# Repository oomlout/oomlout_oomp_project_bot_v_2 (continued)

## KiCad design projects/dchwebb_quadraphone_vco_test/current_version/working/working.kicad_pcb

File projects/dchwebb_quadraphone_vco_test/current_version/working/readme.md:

# quadraphone
 
## summary 
* id: dchwebb_quadraphone_vco_test
* user: dchwebb
* name: quadraphone
* board: vco_test
* repo: https://github.com/dchwebb/Quadraphone
* src_file_repo_kicad_pcb: bu/Test_Board_Final/VCO_Test.kicad_pcb
* src_file_repo_kicad_pcb_link: https://github.com/dchwebb/Quadraphone/tree/main/bu/Test_Board_Final/VCO_Test.kicad_pcb
* src_file_repo_kicad_sch: bu/Test_Board_Final/VCO_Test.kicad_sch
* src_file_repo_kicad_sch_link: https://github.com/dchwebb/Quadraphone/tree/main/bu/Test_Board_Final/VCO_Test.kicad_sch

* src_file_repo_sch: 
* src_file_repo_sch_link: https://github.com/dchwebb/Quadraphone/tree/main/
* full details link: https://github.com/oomlout/oomlout_oomp_project_bot_v_2/tree/main/projects/dchwebb_quadraphone_vco_test/current_version/working

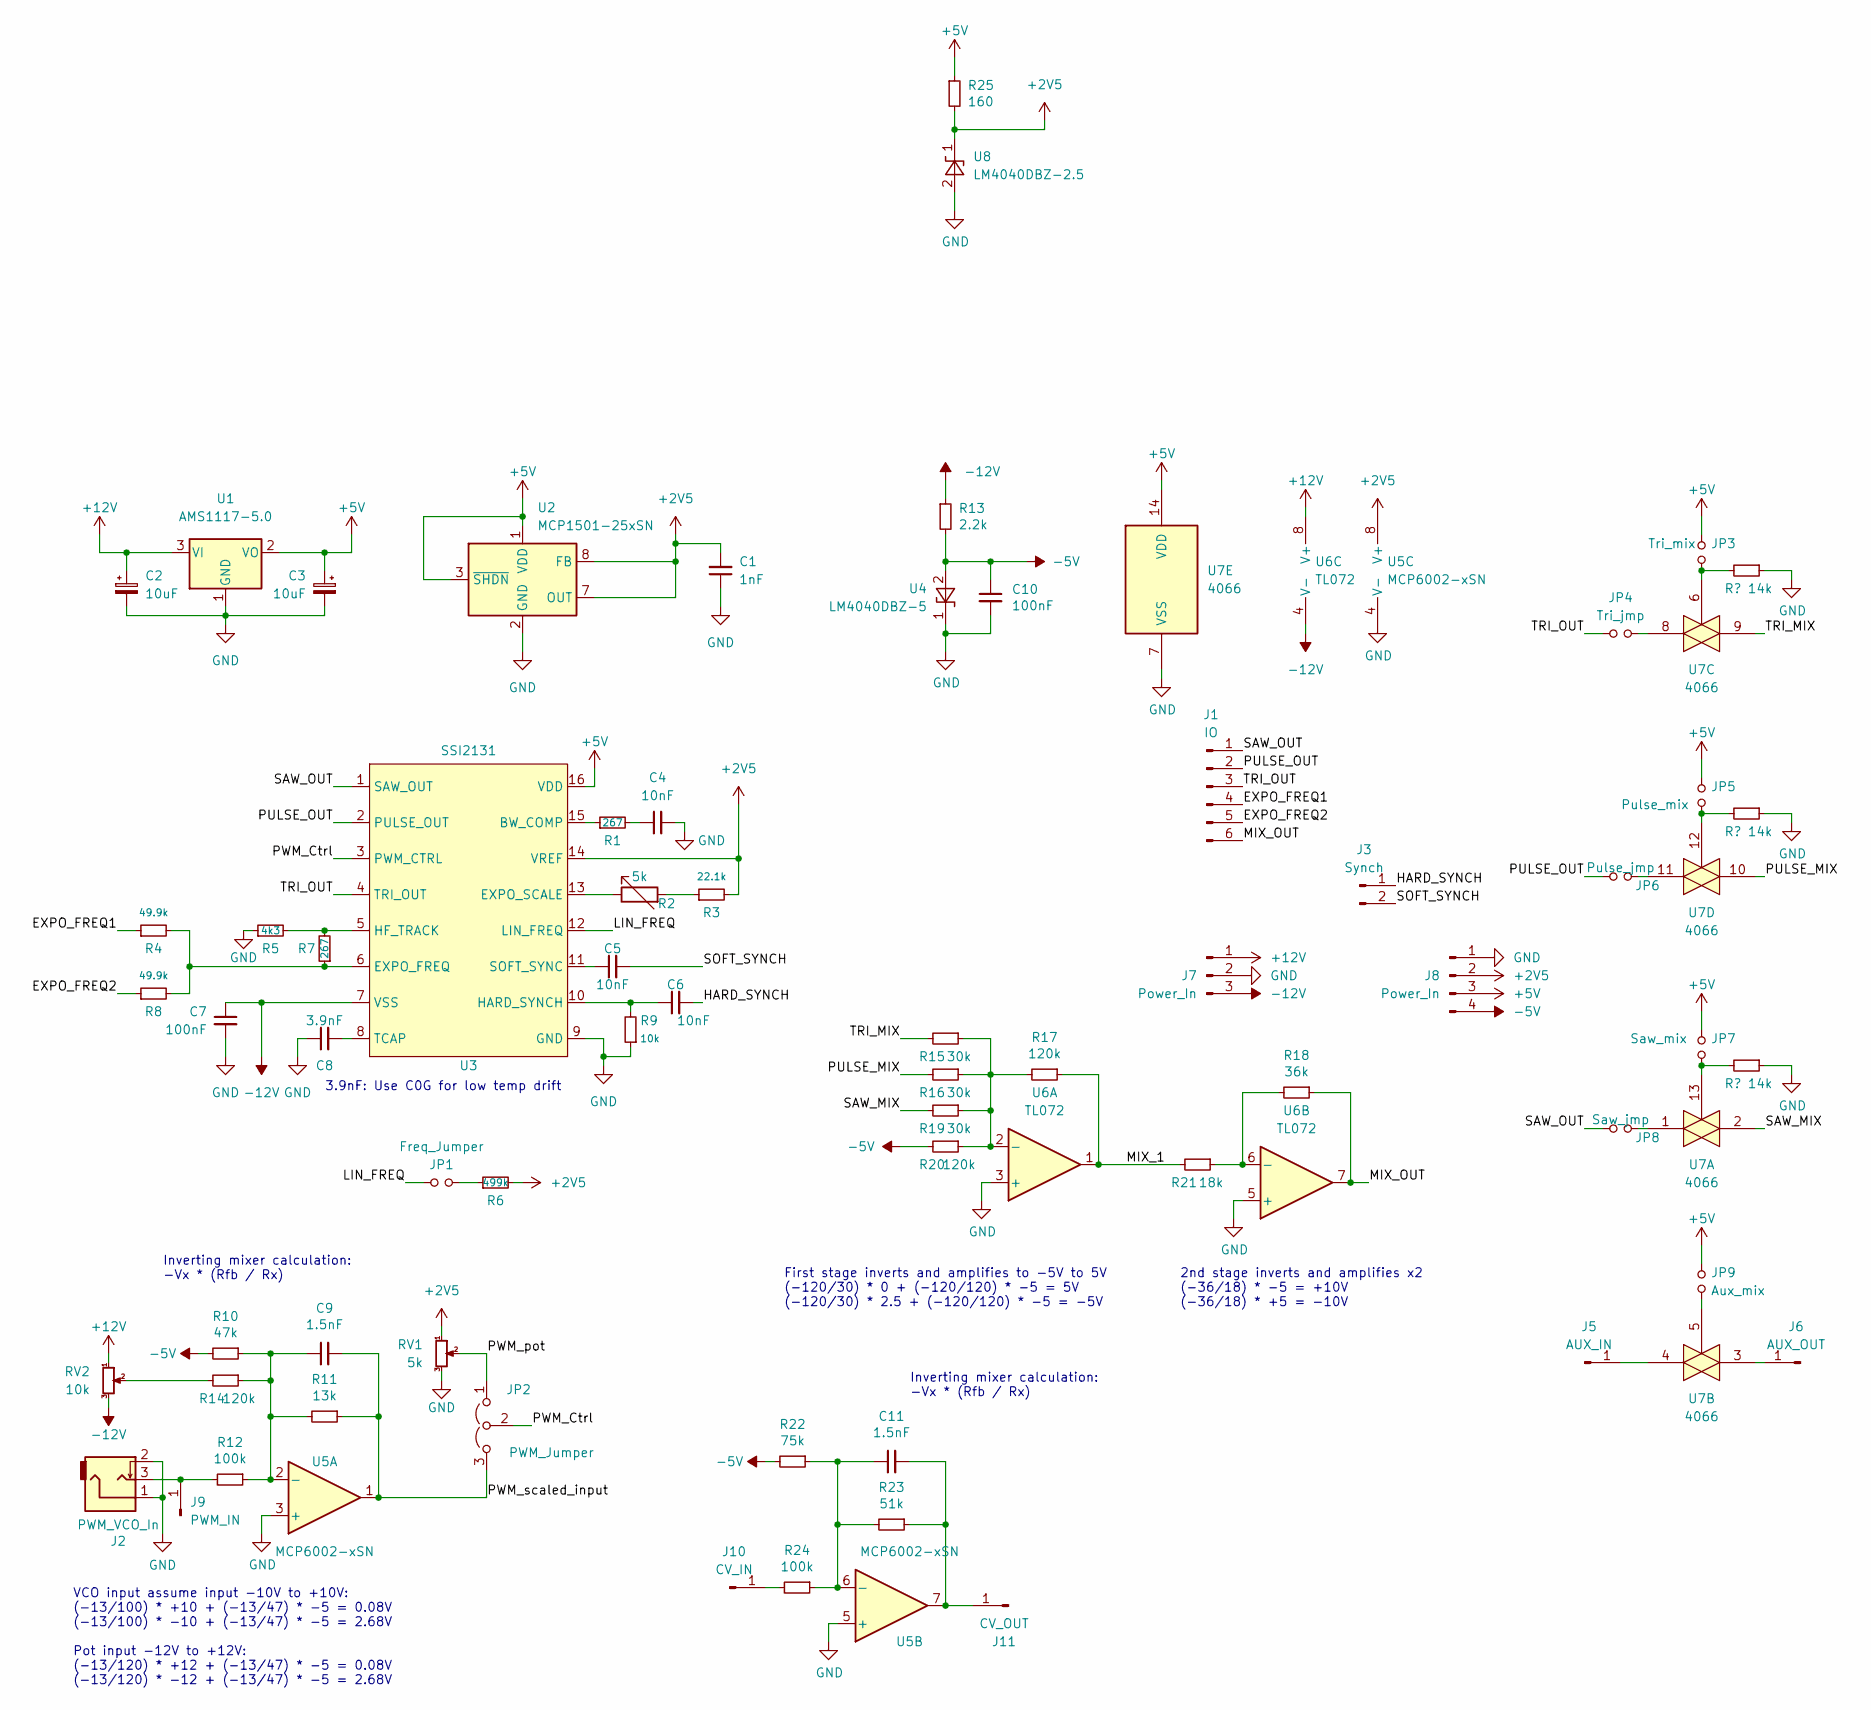
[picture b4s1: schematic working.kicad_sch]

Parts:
C1: 1nF; C_0805_2012Metric
C2, C3: 10uF; CP_Elec_5x5.7
C4, C5, C6: 10nF; C_0805_2012Metric
C7, C10: 100nF; C_0805_2012Metric
C8: 3.9nF; C_0805_2012Metric
C9, C11: 1.5nF; C_0805_2012Metric
J1: IO; PinHeader_1x06_P2.54mm_Vertical
J2: PWM_VCO_In; THONKICONN_hole
J3: Synch; PinHeader_1x02_P2.54mm_Vertical
J5: AUX_IN; PinHeader_1x01_P2.54mm_Vertical
J6: AUX_OUT; PinHeader_1x01_P2.54mm_Vertical
J7: Power_In; PinHeader_1x03_P2.54mm_Vertical
J8: Power_In; PinHeader_1x04_P2.54mm_Vertical
J9: PWM_IN; PinHeader_1x01_P2.54mm_Vertical
J10: CV_IN; PinHeader_1x01_P2.54mm_Vertical
J11: CV_OUT; PinHeader_1x01_P2.54mm_Vertical
JP1: Freq_Jumper; PinHeader_1x02_P2.54mm_Vertical
JP2: PWM_Jumper; PinHeader_1x03_P2.54mm_Vertical
JP3: Tri_mix; PinHeader_1x02_P2.54mm_Vertical
JP4: Tri_jmp; PinHeader_1x02_P2.54mm_Vertical
JP5: Pulse_mix; PinHeader_1x02_P2.54mm_Vertical
JP6: Pulse_jmp; PinHeader_1x02_P2.54mm_Vertical
JP7: Saw_mix; PinHeader_1x02_P2.54mm_Vertical
JP8: Saw_jmp; PinHeader_1x02_P2.54mm_Vertical
JP9: Aux_mix; PinHeader_1x02_P2.54mm_Vertical
R1, R7: 267; R_0805_2012Metric
R2: 5k; Potentiometer_Piher_PT-6-V_Vertical
R3: 22.1k; R_0805_2012Metric
R4, R8: 49.9k; R_0805_2012Metric
R5: 4k3; R_0805_2012Metric
R6: 499k; R_0805_2012Metric
R9: 10k; R_0805_2012Metric
R10: 47k; R_0805_2012Metric
R11: 13k; R_0805_2012Metric
R12, R24: 100k; R_0805_2012Metric
R13: 2.2k; R_0805_2012Metric
R14, R17, R20: 120k; R_0805_2012Metric
R15, R16, R19: 30k; R_0805_2012Metric
R18: 36k; R_0805_2012Metric
R21: 18k; R_0805_2012Metric
R22: 75k; R_0805_2012Metric
R23: 51k; R_0805_2012Metric
R25: 160; R_0805_2012Metric
RV1: 5k; Alpha_9mm_Potentiometer_Aligned
RV2: 10k; Alpha_9mm_Potentiometer_Aligned
U1: AMS1117-5.0; SOT-223-3_TabPin2
U2: MCP1501-25xSN; SOIC-8_3.9x4.9mm_P1.27mm
U3: SSI2131; SOIC-16_3.9x9.9mm_P1.27mm
U4: LM4040DBZ-5; SOT-23
U5: MCP6002-xSN; MSOP-8_3x3mm_P0.65mm
U6: TL072; SO-8_3.9x4.9mm_P1.27mm
U7: 4066; TSSOP-14_4.4x5mm_P0.65mm
U8: LM4040DBZ-2.5; SOT-23

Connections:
+2V5: C1.2, J8.2, R3.2, R6.2, R25.2, RV1.1, U2.7 (OUT), U2.8 (FB), U3.14 (VREF), U5.8 (V+), U8.1 (K)
+5V: C3.1, J8.3, JP3.2, JP5.2, JP7.2, JP9.2, R25.1, U1.2 (VO), U2.1 (VDD), U2.3 (~SHDN), U3.16 (VDD), U7.14 (VDD)
+12V: C2.1, J7.1, RV2.1, U1.3 (VI), U6.8 (V+)
-5V: C10.1, J8.4, R10.2, R13.2, R20.2, R22.2, U4.2 (A)
-12V: C7.1, J7.3, R13.1, RV2.3, U3.7 (VSS), U6.4 (V-)
/EXPO_FREQ1: J1.4, R4.1
/EXPO_FREQ2: J1.5, R8.1
/HARD_SYNCH: C6.2, J3.1
/LIN_FREQ: JP1.1, U3.12 (LIN_FREQ)
/MIX_1: R17.1, R21.2, U6.1
/MIX_OUT: J1.6, R18.1, U6.7
/PULSE_MIX: R16.2, U7.10
/PULSE_OUT: J1.2, JP6.1, U3.2 (PULSE_OUT)
/PWM_Ctrl: JP2.2 (C), U3.3 (PWM_CTRL)
/PWM_pot: JP2.1 (A), RV1.2
/PWM_scaled_input: C9.2, JP2.3 (B), R11.1, U5.1
/SAW_MIX: R19.2, U7.2
/SAW_OUT: J1.1, JP8.1, U3.1 (SAW_OUT)
/SOFT_SYNCH: C5.2, J3.2
/TRI_MIX: R15.2, U7.9
/TRI_OUT: J1.3, JP4.1, U3.4 (TRI_OUT)
GND: C1.1, C2.2, C3.2, C4.2, C7.2, C8.1, C10.2, J2.1, J2.2, J7.2, J8.1, R5.1, R9.1, RV1.3, U1.1 (GND), U2.2 (GND), U2.4 (GND), U2.5 (GND), U2.6 (GND), U3.9 (GND), U4.1 (K), U5.3 (+), U5.4 (V-), U5.5 (+), U6.3 (+), U6.5 (+), U7.7 (VSS), U8.2 (A)
unnamed: C4.1, R1.2
unnamed: C5.1, U3.11 (SOFT_SYNC)
unnamed: C6.1, R9.2, U3.10 (HARD_SYNCH)
unnamed: C8.2, U3.8 (TCAP)
unnamed: C9.1, R10.1, R11.2, R12.1, R14.1, U5.2 (-)
unnamed: C11.1, R22.1, R23.2, R24.1, U5.6 (-)
unnamed: C11.2, J11.1, R23.1, U5.7
unnamed: J2.3, J9.1, R12.2
unnamed: J5.1, U7.4
unnamed: J6.1, U7.3
unnamed: J10.1, R24.2
unnamed: JP1.2, R6.1
unnamed: JP3.1, U7.6
unnamed: JP4.2, U7.8
unnamed: JP5.1, U7.12
unnamed: JP6.2, U7.11
unnamed: JP7.1, U7.13
unnamed: JP8.2, U7.1
unnamed: JP9.1, U7.5
unnamed: R1.1, U3.15 (BW_COMP)
unnamed: R2.1, U3.13 (EXPO_SCALE)
unnamed: R2.2, R3.1
unnamed: R4.2, R7.1, R8.2, U3.6 (EXPO_FREQ)
unnamed: R5.2, R7.2, U3.5 (HF_TRACK)
unnamed: R14.2, RV2.2
unnamed: R15.1, R16.1, R17.2, R19.1, R20.1, U6.2 (-)
unnamed: R18.2, R21.1, U6.6 (-)

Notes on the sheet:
VCO input assume input -10V to +10V: (-13/100) * +10 + (-13/47) * -5 = 0.08V (-13/100) * -10 + (-13/47) * -5 = 2.68V Pot input -12V to +12V: (-13/120) * +12 + (-13/47) * -5 = 0.08V (-13/120) * -12 + (-13/47) * -5 = 2.68V
First stage inverts and amplifies to -5V to 5V (-120/30) * 0 + (-120/120) * -5 = 5V (-120/30) * 2.5 + (-120/120) * -5 = -5V
3.9nF: Use C0G for low temp drift
2nd stage inverts and amplifies x2 (-36/18) * -5 = +10V (-36/18) * +5 = -10V
Inverting mixer calculation: -Vx * (Rfb / Rx)

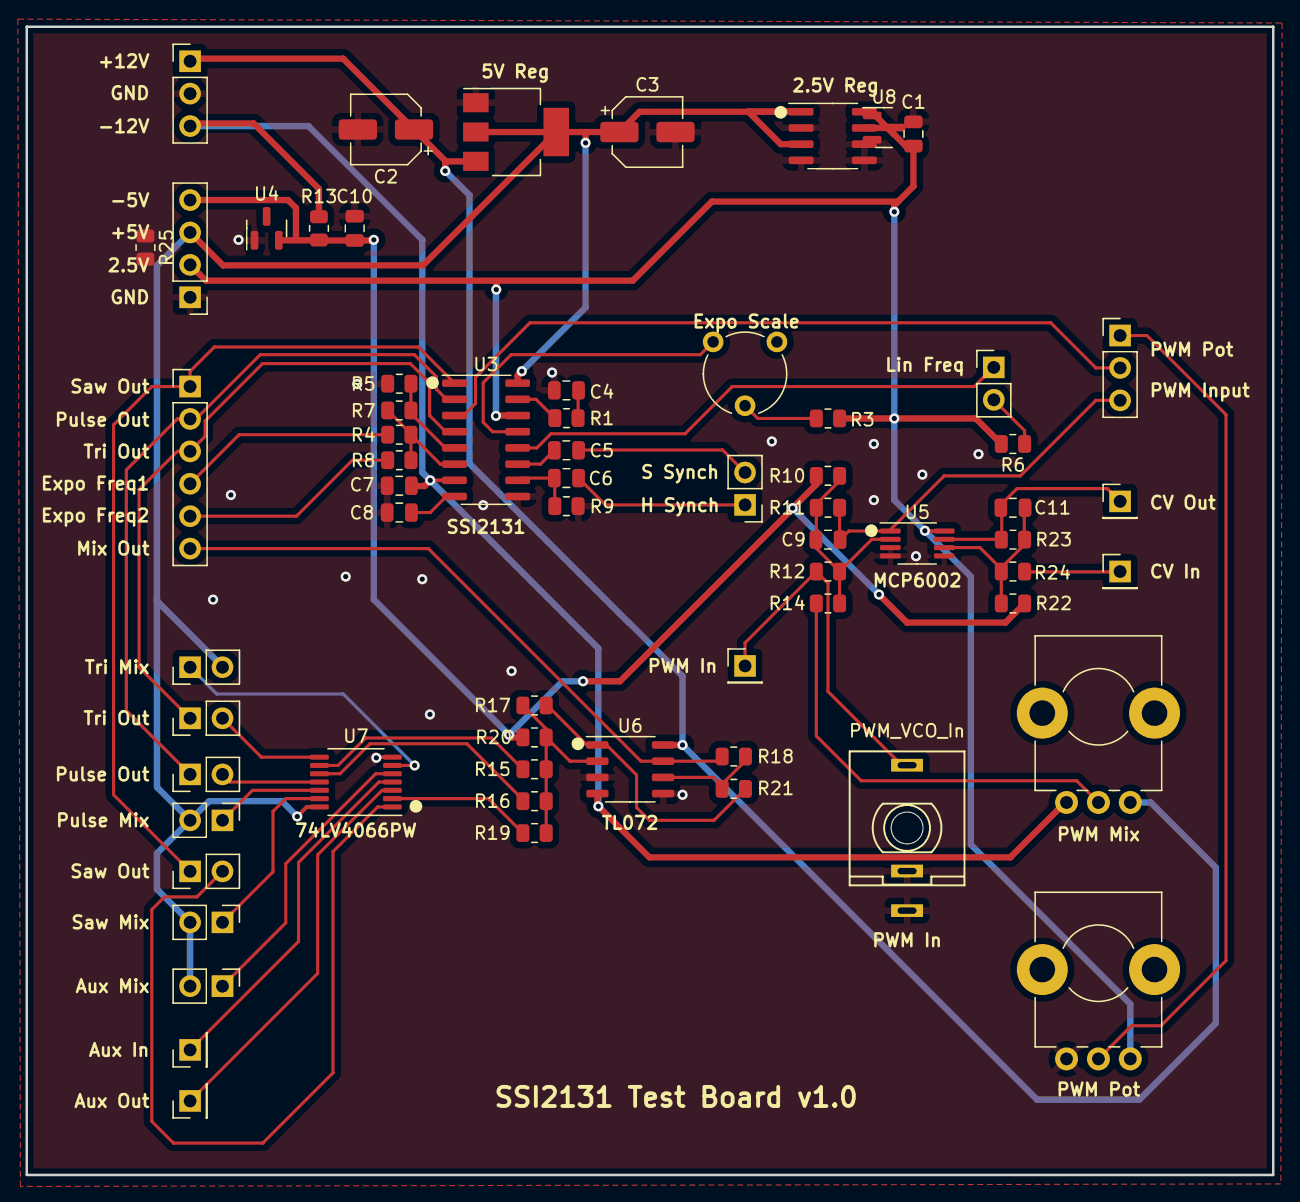
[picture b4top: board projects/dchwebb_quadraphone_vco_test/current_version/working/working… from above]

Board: 2 copper layers, 97.7 x 90.0 mm, 65 parts (0 on the bottom side), 49 nets.

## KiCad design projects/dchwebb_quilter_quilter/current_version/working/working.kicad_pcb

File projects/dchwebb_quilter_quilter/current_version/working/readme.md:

# quilter
 
## summary 
* id: dchwebb_quilter_quilter
* user: dchwebb
* name: quilter
* board: quilter
* repo: https://github.com/dchwebb/Quilter
* src_file_repo_kicad_pcb: Test_Board/Quilter.kicad_pcb
* src_file_repo_kicad_pcb_link: https://github.com/dchwebb/Quilter/tree/main/Test_Board/Quilter.kicad_pcb
* src_file_repo_kicad_sch: Test_Board/Quilter.kicad_sch
* src_file_repo_kicad_sch_link: https://github.com/dchwebb/Quilter/tree/main/Test_Board/Quilter.kicad_sch

* src_file_repo_sch: 
* src_file_repo_sch_link: https://github.com/dchwebb/Quilter/tree/main/
* full details link: https://github.com/oomlout/oomlout_oomp_project_bot_v_2/tree/main/projects/dchwebb_quilter_quilter/current_version/working

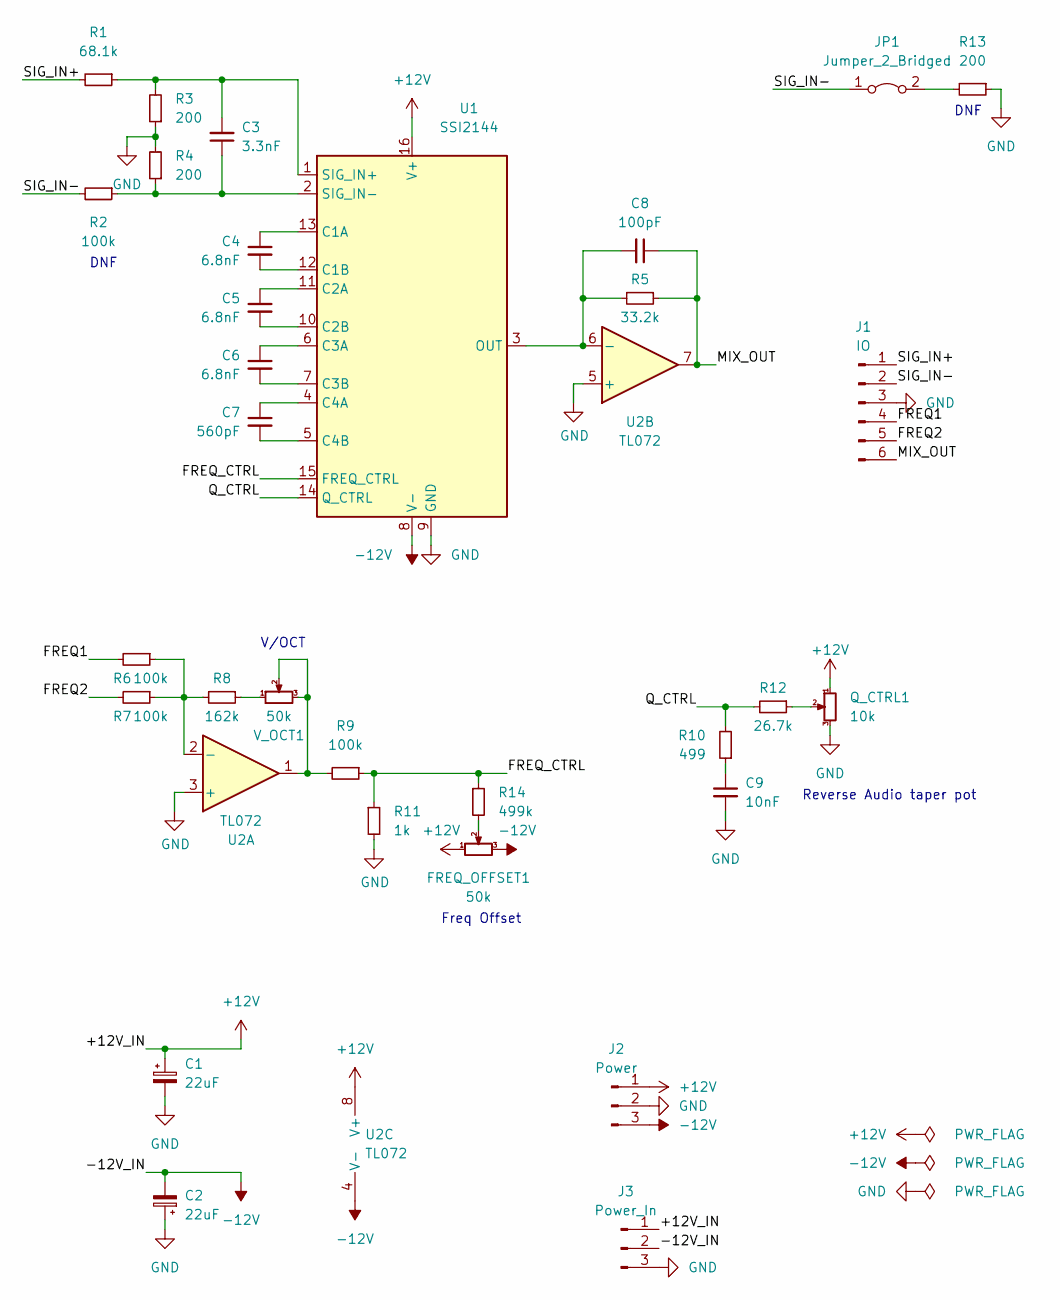
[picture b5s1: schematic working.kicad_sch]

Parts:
C1: 22uF; CP_Elec_5x5.7; Part_Number C134798
C2: 22uF; CP_Elec_5x5.7; Part_Number C134793
C3: 3.3nF; C_0603_1608Metric_Pad1.08x0.95mm_HandSolder
C4, C5, C6: 6.8nF; C_0603_1608Metric_Pad1.08x0.95mm_HandSolder
C7: 560pF; C_0603_1608Metric_Pad1.08x0.95mm_HandSolder
C8: 100pF; C_0805_2012Metric
C9: 10nF; C_0603_1608Metric_Pad1.08x0.95mm_HandSolder
FREQ_OFFSET1: 50k; Alpha_9mm_Potentiometer_Aligned
J1: IO; PinHeader_1x06_P2.54mm_Vertical
J2: Power; PinHeader_1x03_P2.54mm_Vertical
J3: Power_In; PinHeader_1x03_P2.54mm_Vertical
JP1: Jumper_2_Bridged; SolderJumper-2_P1.3mm_Bridged_RoundedPad1.0x1.5mm
Q_CTRL1: 10k; Alpha_9mm_Potentiometer_Aligned
R1: 68.1k; R_0805_2012Metric
R2, R6, R7, R9: 100k; R_0805_2012Metric
R3, R4, R13: 200; R_0805_2012Metric
R5: 33.2k; R_0805_2012Metric
R8: 162k; R_0805_2012Metric
R10: 499; R_0805_2012Metric
R11: 1k; R_0805_2012Metric
R12: 26.7k; R_0805_2012Metric
R14: 499k; R_0805_2012Metric
U1: SSI2144; SSOP-16_3.9x4.9mm_P0.635mm
U2: TL072; SO-8_3.9x4.9mm_P1.27mm
V_OCT1: 50k; Alpha_9mm_Potentiometer_Aligned

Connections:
+12V: C1.1, FREQ_OFFSET1.1, J2.1, J3.1, Q_CTRL1.1, U1.16 (V+), U2.8 (V+)
-12V: C2.2, FREQ_OFFSET1.3, J2.3, J3.2, U1.8 (V-), U2.4 (V-)
/FREQ1: J1.4, R6.2
/FREQ2: J1.5, R7.2
/FREQ_CTRL: R9.1, R11.1, R14.1, U1.15 (FREQ_CTRL)
/MIX_OUT: C8.1, J1.6, R5.1, U2.7
/Q_CTRL: R10.2, R12.2, U1.14 (Q_CTRL)
/SIG_IN+: J1.1, R1.2
/SIG_IN-: J1.2, JP1.1 (A), R2.2
GND: C1.2, C2.1, C9.2, J1.3, J2.2, J3.3, Q_CTRL1.3, R3.1, R4.2, R11.2, R13.1, U1.9 (GND), U2.3 (+), U2.5 (+)
unnamed: C3.1, R2.1, R4.1, U1.2 (SIG_IN-)
unnamed: C3.2, R1.1, R3.2, U1.1 (SIG_IN+)
unnamed: C4.1, U1.13 (C1A)
unnamed: C4.2, U1.12 (C1B)
unnamed: C5.1, U1.11 (C2A)
unnamed: C5.2, U1.10 (C2B)
unnamed: C6.1, U1.6 (C3A)
unnamed: C6.2, U1.7 (C3B)
unnamed: C7.1, U1.4 (C4A)
unnamed: C7.2, U1.5 (C4B)
unnamed: C8.2, R5.2, U1.3 (OUT), U2.6 (-)
unnamed: C9.1, R10.1
unnamed: FREQ_OFFSET1.2, R14.2
unnamed: JP1.2 (B), R13.2
unnamed: R6.1, R7.1, R8.2, U2.2 (-)
unnamed: R8.1, V_OCT1.1
unnamed: R9.2, U2.1, V_OCT1.2, V_OCT1.3
unnamed: Q_CTRL1.2, R12.1

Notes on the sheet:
Freq Offset
DNF
V/OCT
Reverse Audio taper pot

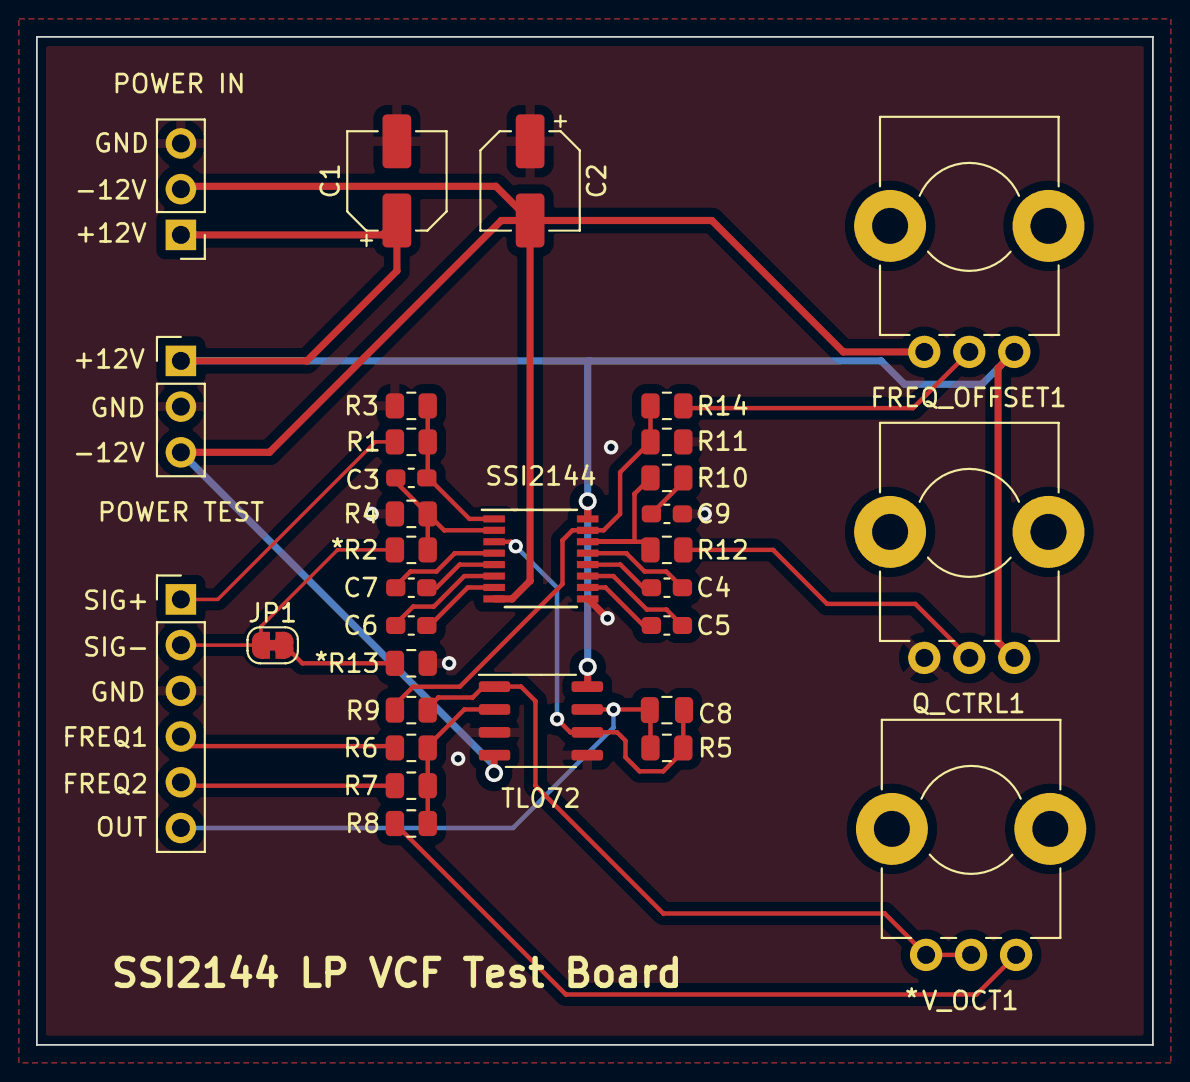
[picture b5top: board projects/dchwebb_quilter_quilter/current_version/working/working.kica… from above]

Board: 2 copper layers, 62.0 x 56.0 mm, 32 parts (0 on the bottom side), 28 nets.
